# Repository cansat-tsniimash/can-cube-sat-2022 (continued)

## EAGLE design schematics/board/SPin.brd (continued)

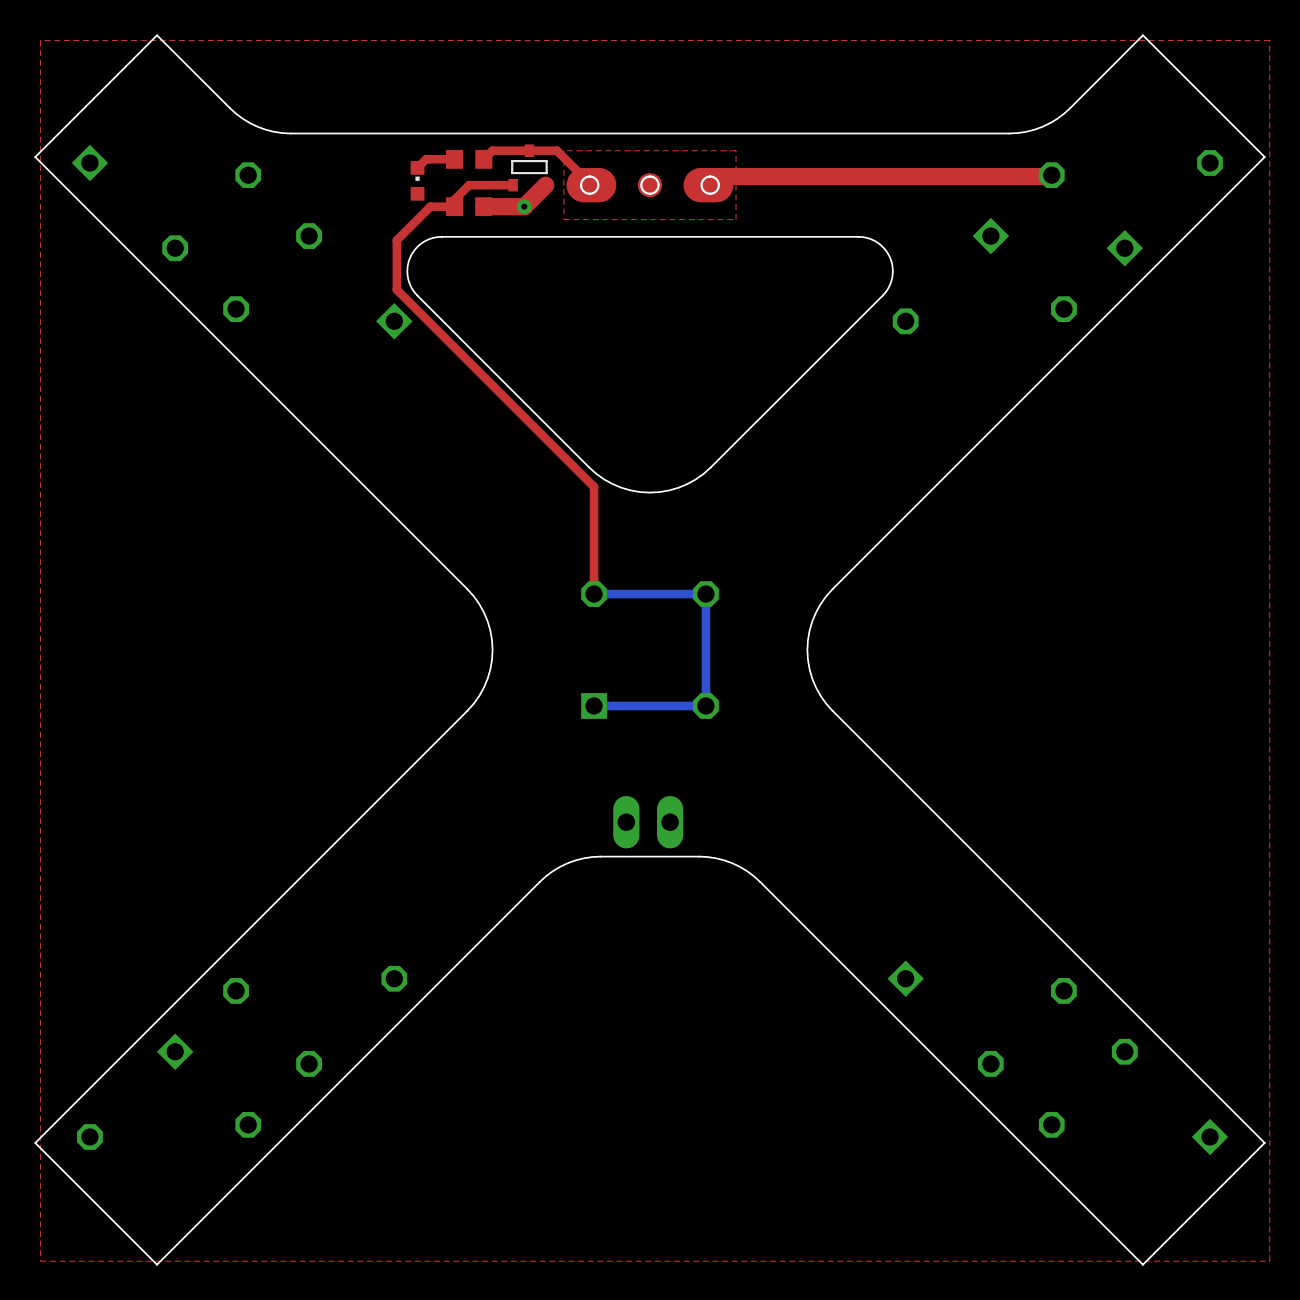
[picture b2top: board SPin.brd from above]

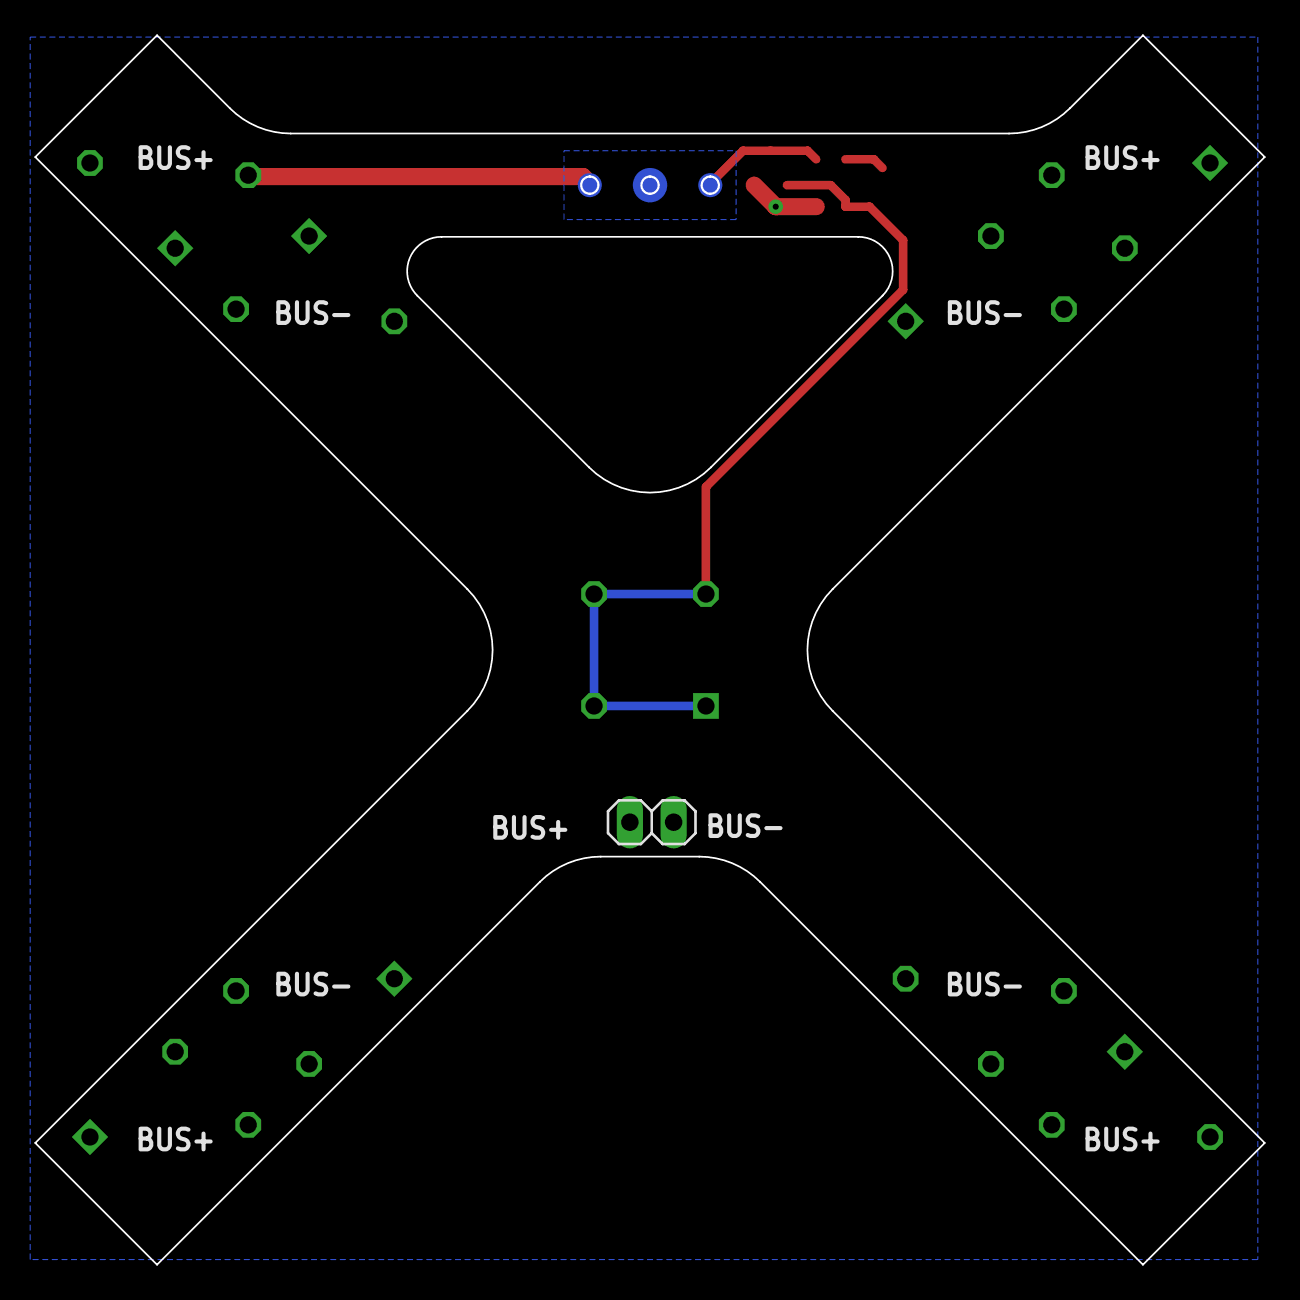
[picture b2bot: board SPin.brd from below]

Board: 2 copper layers, 71.4 x 71.4 mm, 15 parts (9 on the bottom side), 5 nets.

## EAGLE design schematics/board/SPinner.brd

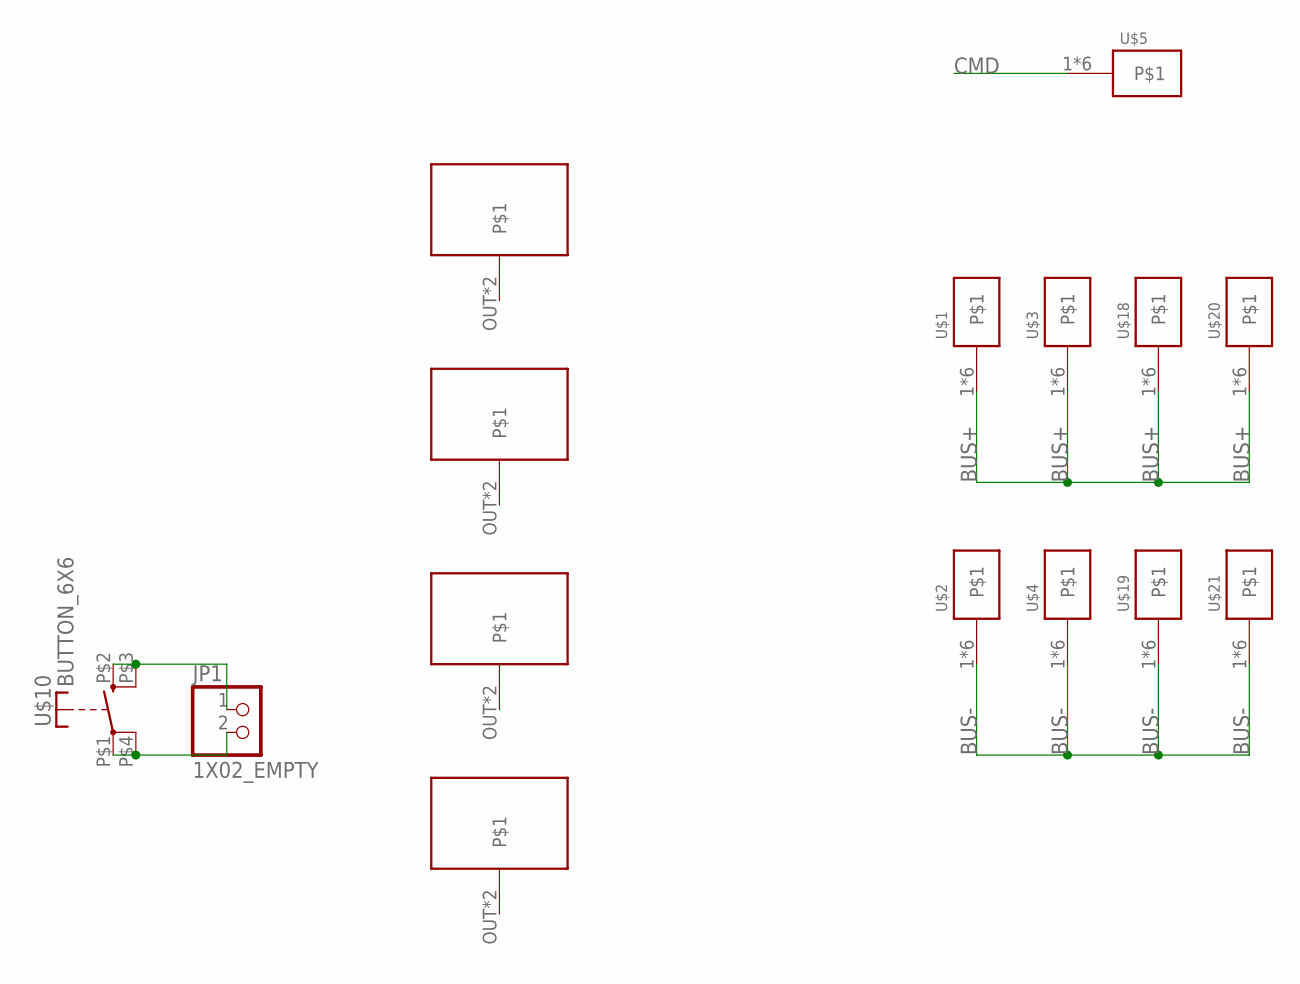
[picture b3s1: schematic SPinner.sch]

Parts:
JP1: 1X02_EMPTY
U$1, U$2, U$3, U$4, U$18, U$19, U$20, U$21: KCONNECT
U$5: KCONNECTQUAD; KCONNECT_QUAD
U$6, U$7, U$8, U$9: GRAFIT-PASSIVE
U$10: BUTTON_6X6

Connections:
BUS+: U$1.1, U$1.2, U$1.3, U$1.4, U$1.P$1, U$1.P$2, U$3.1, U$3.2, U$3.3, U$3.4, U$3.P$1, U$3.P$2, U$18.1, U$18.2, U$18.3, U$18.4, U$18.P$1, U$18.P$2, U$20.1, U$20.2, U$20.3, U$20.4, U$20.P$1, U$20.P$2
BUS-: U$2.1, U$2.2, U$2.3, U$2.4, U$2.P$1, U$2.P$2, U$4.1, U$4.2, U$4.3, U$4.4, U$4.P$1, U$4.P$2, U$19.1, U$19.2, U$19.3, U$19.4, U$19.P$1, U$19.P$2, U$21.1, U$21.2, U$21.3, U$21.4, U$21.P$1, U$21.P$2
CMD: U$5.1, U$5.2, U$5.3, U$5.4, U$5.P$1, U$5.P$2
unnamed: JP1.1, U$10.P$2 (S), U$10.P$3 (S)
unnamed: JP1.2, U$10.P$1, U$10.P$4

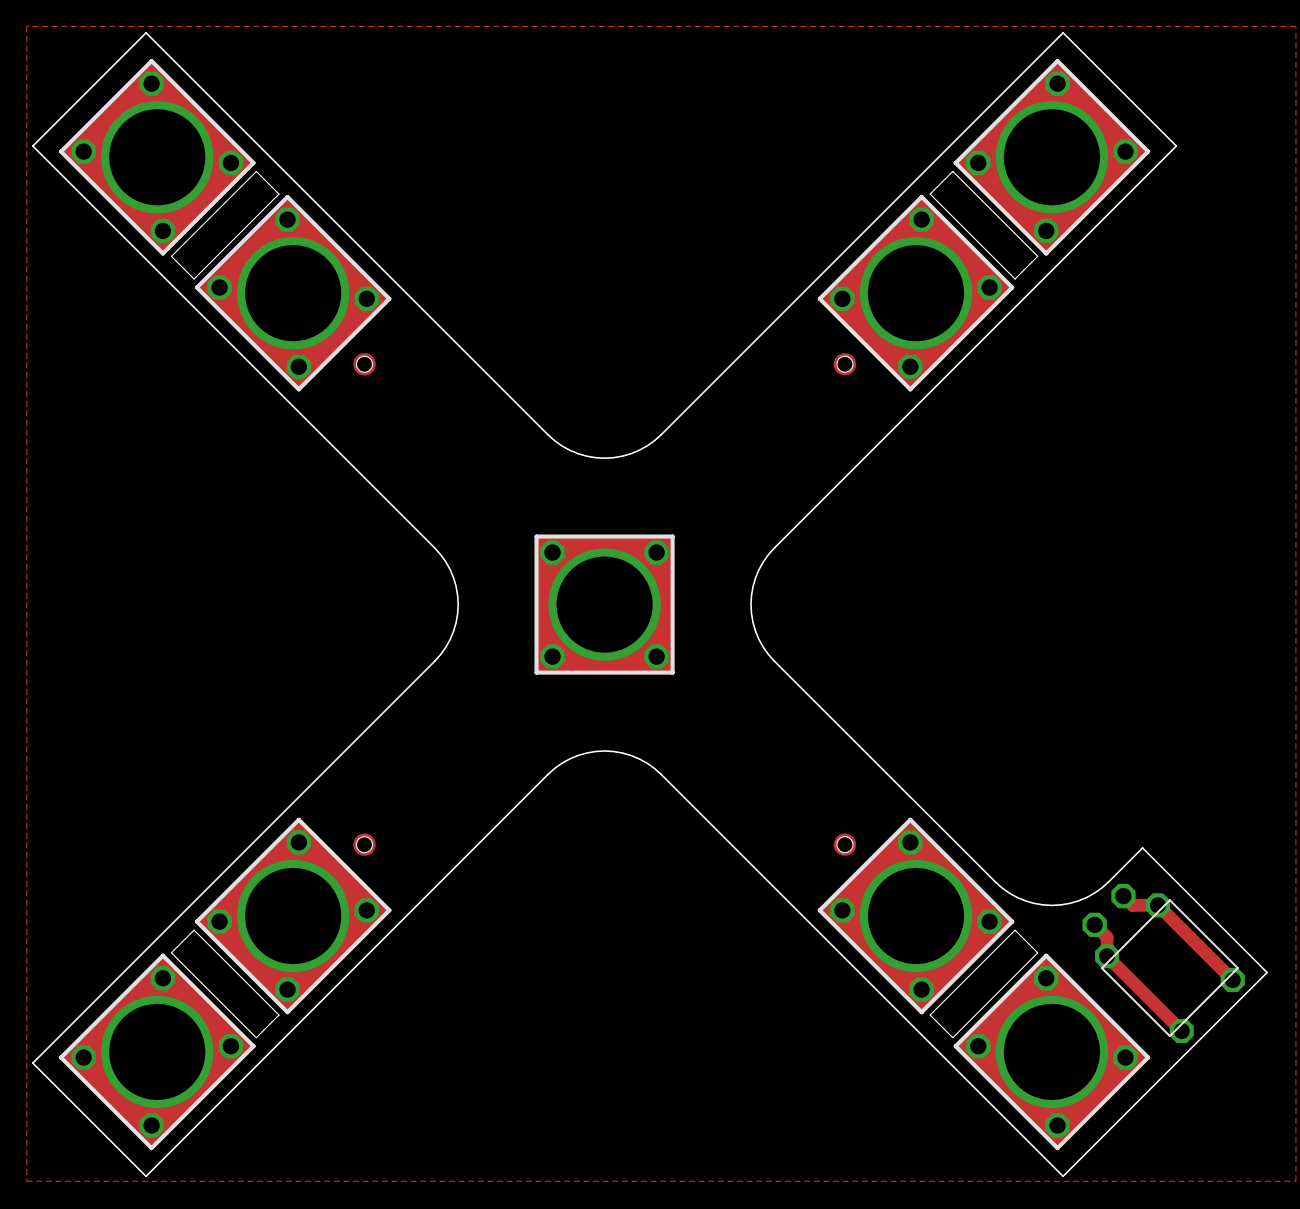
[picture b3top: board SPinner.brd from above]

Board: 2 copper layers, 77.1 x 71.4 mm, 15 parts (0 on the bottom side), 5 nets.

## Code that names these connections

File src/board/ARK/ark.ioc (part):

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Mcu.Name=STM32F103C(8-B)Tx
Mcu.Package=LQFP48
Mcu.UserName=STM32F103C8Tx
PA0-WKUP.GPIOParameters=GPIO_Speed,PinState,GPIO_PuPd,GPIO_Label,GPIO_ModeDefaultOutputPP
PA0-WKUP.GPIO_Label=BMS4
PA0-WKUP.GPIO_ModeDefaultOutputPP=GPIO_MODE_OUTPUT_OD
PA0-WKUP.GPIO_PuPd=GPIO_NOPULL
PA0-WKUP.GPIO_Speed=GPIO_SPEED_FREQ_LOW
PA0-WKUP.PinState=GPIO_PIN_SET
PA0-WKUP.Signal=GPIO_Output
PA1.GPIOParameters=GPIO_Speed,PinState,GPIO_PuPd,GPIO_Label,GPIO_ModeDefaultOutputPP
PA1.GPIO_Label=BMS1
PA1.GPIO_ModeDefaultOutputPP=GPIO_MODE_OUTPUT_OD
PA1.GPIO_PuPd=GPIO_NOPULL
PA1.GPIO_Speed=GPIO_SPEED_FREQ_LOW
PA1.PinState=GPIO_PIN_SET
PA1.Signal=GPIO_Output
PA10.Mode=Asynchronous
PA10.Signal=USART1_RX
PA13.Mode=Serial_Wire
PA13.Signal=SYS_JTMS-SWDIO
PA14.Mode=Serial_Wire
PA14.Signal=SYS_JTCK-SWCLK
PA15.GPIOParameters=GPIO_Label
PA15.GPIO_Label=DC_DC
PA15.Signal=GPIO_Output
PA2.GPIOParameters=GPIO_Speed,PinState,GPIO_PuPd,GPIO_Label,GPIO_ModeDefaultOutputPP
PA2.GPIO_Label=BMS2
PA2.GPIO_ModeDefaultOutputPP=GPIO_MODE_OUTPUT_OD
PA2.GPIO_PuPd=GPIO_NOPULL
PA2.GPIO_Speed=GPIO_SPEED_FREQ_LOW
PA2.PinState=GPIO_PIN_SET
PA2.Signal=GPIO_Output
PA3.GPIOParameters=GPIO_Label
PA3.GPIO_Label=TIME
PA3.Signal=GPXTI3
PA4.GPIOParameters=GPIO_Label,GPIO_Speed,GPIO_ModeDefaultOutputPP,PinState,GPIO_PuPd
PA4.GPIO_Label=OW
PA4.GPIO_ModeDefaultOutputPP=GPIO_MODE_OUTPUT_OD
PA4.GPIO_PuPd=GPIO_NOPULL
PA4.GPIO_Speed=GPIO_SPEED_FREQ_HIGH
PA4.PinState=GPIO_PIN_SET
PA4.Signal=GPIO_Output
PA5.GPIOParameters=GPIO_Label
PA5.GPIO_Label=ROZE1
PA5.Signal=GPIO_Input
PA6.GPIOParameters=GPIO_Label
PA6.GPIO_Label=ROZE2
PA6.Signal=GPIO_Input
PA7.GPIOParameters=GPIO_Label
PA7.GPIO_Label=ROZE3
PA7.Signal=GPIO_Input
PA8.GPIOParameters=GPIO_Label
PA8.GPIO_Label=PFI_C
PA8.Signal=GPXTI8
PA9.Mode=Asynchronous
PA9.Signal=USART1_TX
PB0.GPIOParameters=GPIO_Label
PB0.GPIO_Label=ROZE4
PB0.Signal=GPIO_Input
PB10.GPIOParameters=GPIO_Label,GPIO_Pu
PB10.GPIO_Label=SCL
PB10.GPIO_Pu=GPIO_PULLUP
PB10.Mode=I2C
PB10.Signal=I2C2_SCL
PB11.GPIOParameters=GPIO_Label,GPIO_Pu
PB11.GPIO_Label=SDA
PB11.GPIO_Pu=GPIO_PULLUP
PB11.Mode=I2C
PB11.Signal=I2C2_SDA
PB12.GPIOParameters=GPIO_Label,GPIO_Speed,GPIO_ModeDefaultOutputPP,PinState,GPIO_PuPd
PB12.GPIO_Label=LED
PB12.GPIO_ModeDefaultOutputPP=GPIO_MODE_OUTPUT_OD
PB12.GPIO_PuPd=GPIO_NOPULL
PB12.GPIO_Speed=GPIO_SPEED_FREQ_LOW
PB12.PinState=GPIO_PIN_SET
PB12.Signal=GPIO_Output
PB13.GPIOParameters=GPIO_Label
PB13.GPIO_Label=INT_C
PB13.Signal=GPXTI13
PB14.GPIOParameters=GPIO_Label
PB14.GPIO_Label=PGB_C
PB14.Signal=GPXTI14
PB15.GPIOParameters=GPIO_Label
PB15.GPIO_Label=PGS_C
PB15.Signal=GPXTI15
PB4.GPIOParameters=GPIO_Label
PB4.GPIO_Label=PFI_D
PB4.Signal=GPXTI4
PB5.GPIOParameters=GPIO_Label
PB5.GPIO_Label=INT_D
PB5.Signal=GPXTI5
PB6.GPIOParameters=GPIO_Label
PB6.GPIO_Label=PGB_D
PB6.Signal=GPXTI6
PB7.GPIOParameters=GPIO_Label
PB7.GPIO_Label=PGS_D
PB7.Signal=GPXTI7
PB8.GPIOParameters=GPIO_Label,GPIO_Pu
PB8.GPIO_Label=SCLTM
PB8.GPIO_Pu=GPIO_PULLUP
PB8.Mode=I2C
PB8.Signal=I2C1_SCL
PB9.GPIOParameters=GPIO_Label,GPIO_Pu
PB9.GPIO_Label=SDATM
PB9.GPIO_Pu=GPIO_PULLUP
PB9.Mode=I2C
PB9.Signal=I2C1_SDA
PC13-TAMPER-RTC.GPIOParameters=GPIO_Speed,PinState,GPIO_PuPd,GPIO_Label,GPIO_ModeDefaultOutputPP
PC13-TAMPER-RTC.GPIO_Label=BMS5
PC13-TAMPER-RTC.GPIO_ModeDefaultOutputPP=GPIO_MODE_OUTPUT_OD
PC13-TAMPER-RTC.GPIO_PuPd=GPIO_NOPULL
PC13-TAMPER-RTC.GPIO_Speed=GPIO_SPEED_FREQ_LOW
PC13-TAMPER-RTC.PinState=GPIO_PIN_SET
PC13-TAMPER-RTC.Signal=GPIO_Output
PC14-OSC32_IN.GPIOParameters=GPIO_Speed,PinState,GPIO_PuPd,GPIO_Label,GPIO_ModeDefaultOutputPP
PC14-OSC32_IN.GPIO_Label=BMS6
PC14-OSC32_IN.GPIO_ModeDefaultOutputPP=GPIO_MODE_OUTPUT_OD
PC14-OSC32_IN.GPIO_PuPd=GPIO_NOPULL
PC14-OSC32_IN.GPIO_Speed=GPIO_SPEED_FREQ_LOW
PC14-OSC32_IN.PinState=GPIO_PIN_SET
PC14-OSC32_IN.Signal=GPIO_Output
PC15-OSC32_OUT.GPIOParameters=GPIO_Speed,PinState,GPIO_PuPd,GPIO_Label,GPIO_ModeDefaultOutputPP
PC15-OSC32_OUT.GPIO_Label=BMS3
PC15-OSC32_OUT.GPIO_ModeDefaultOutputPP=GPIO_MODE_OUTPUT_OD
PC15-OSC32_OUT.GPIO_PuPd=GPIO_NOPULL
PC15-OSC32_OUT.GPIO_Speed=GPIO_SPEED_FREQ_LOW
PC15-OSC32_OUT.PinState=GPIO_PIN_SET
PC15-OSC32_OUT.Signal=GPIO_Output
RCC.SYSCLKFreq_VALUE=64000000
RCC.SYSCLKSource=RCC_SYSCLKSOURCE_PLLCLK
board=custom

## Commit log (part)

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2021-05-09 Замдляем I2C
2021-05-09 Тонкие настройки
2021-05-11 Зачатки проекта для имитатора барометров и прочего
2021-05-12 Добавлена шелкографика на плате БКУ
2021-05-12 Симуляция для алгоритма управления компрессором
2021-05-13 Исправлены тайминги отправки пакетов
2021-05-13 Добавлены герберы плат BKU и Debug
2021-05-14 Выставляется правильное время в сообщениях о диодах в синсе
2021-05-14 исправил какой-то косяк с тулчейном для синса
2021-05-15 Коррекция времени работет
2021-05-15 Причесывание GPS в синсе, Работа еще не окончена
2021-05-15 Исправлено напряжение TCXO для радио, согласно мануалу (не очень понятно откуда он взялся...)
2021-05-16 ПН работа
2021-05-16 Очень неприятный баг, который опять пропустили из-за обилия варнингов
2021-05-16 Настройки тулчейна пейлоада опять сползли
2021-05-16 Убрал подозрительные места с работой по невыровненным членам структур. сырое значение MICS6814 теперь сырое значение АЦП, а измеренного сопротивления TODO: перебить поле на инт
2021-05-16 Чуточку причесаны ДНК и дозиметр
2021-05-16 Попытка сделать i2c линк правильно и подключить его к комиссару
2021-05-19 Подтяжка на UART4 RX (отладочный) для пейлоада
2021-05-19 Исправлены баги на пл
2021-05-19 Исправлены ошибки подсчета RSSI в радио-сервере
2021-05-22 Убрал подтяжку
2021-05-22 Отовсюду убраны подтяжки, в пейлоаде выловлено несколько багов и починнен (вроде как) файл проекта
2021-05-22 Вернул таск управления батарейками. Он был отключен здесь 438129f4b1aff372015f85f637c77f4349155d02
2021-05-22 Вернул 2 ины. Были убраны здесь b21d58dcb7bf618727028e3295f56fd343d0ac48
2021-05-22 Баг с дискретной темературой
2021-05-24 Исправлено UB в драйвере радио. Добавлены RSSI в сервер-радио
2021-05-25 Причесал и чуток запараноил драйвер радио
2021-05-26 Убрал варнинги из драйвера радио
2021-05-26 Дополнительный пин для синхронизации времени
2021-05-28 Нехороший косяк в пейлоаде с i2c-линком и мелкая правка утилиты для разбора метаданных ZMQ
2021-05-28 Второе рождение проекта для отладки i2c-link-а на f4
2021-05-29 Добавлены адреса 1w датчиков для арка на стенде
2021-05-29 Да здраствет передача земля - борт
2021-05-29 Исправлена очень страшная бага с одновремененым доступом к шине
2021-05-29 I2C линк доведен до уровня на котором он может быть внедрен в проекты бортового ПО
2021-05-29 Миграция пейлоада на новый i2c-link
2021-05-29 Миграция БКУ новый i2c-link протокол
2021-05-30 Актуализация для отладки its-i2c линка на stm32f1
2021-05-30 Обновление i2c-link драйвера в проектах ПО бортовых компов с поддержкой f1 и f4
2021-05-30 Ошибка в расчете собственной температуры пейлоада
2021-05-31 Переезд наземных утилиток в отдельную папочку
2021-06-03 Дописал гитингор для тестовых проектов
2021-06-03 Готова плата RADIO и переделана плата AB
2021-06-03 Новый i2c линк отлажен на синсе
2021-06-03 Новый драйвер АЦП для полезной нагрузки с компенсацией по напряжению на VDDA
2021-06-03 Отчёты комиссара в полезной нагрузке
2021-06-04 Новый алгоритм управления компрессором
2021-06-04 Добавление стабильного времени во все сообщения полезной нагрузки
2021-06-05 Обновлен счетчик резетов, добавлена причина резета. Перетянуты функции чтения и записи в бэкап регистр RTC из LL драйвера
2021-06-05 Мелкие баги в комиссаре
2021-06-05 БКУ в реалиях стабильного времени в каждом сообщении
2021-06-05 Время теперь синхронизиурется
2021-06-05 Новая политика службы времени на полезной нагрузке и расширение её статуса
2021-06-05 Попытка добавить ины
2021-06-05 Улучшения политики работы со службой времени на полезной нагрузке
2021-06-08 MICS6814 меряет на всех доступных плечах
2021-06-09 Не то, чтобы это было страшные баги с радио, но мелочи, которые требовали правки
2021-06-10 Очень нехорошие баги в brd части радио на бку
2021-06-10 Попытка избежать гонки с завершением rx режима с радио на борту
2021-06-10 Истеричные попытки наладить радиоканал
2021-06-10 Грядет большая революция в драйвере радио
2021-06-11 Добавлен вочдог на sins. Необходимо проверить его работу
2021-06-11 Изменены настройки частот для работы с платой
2021-06-11 ARK переехал на плату. Настроен HSE
2021-06-11 обновлены LL драйверы для rtc-fromgps
2021-06-12 Кажется, лучше не становится
2021-06-12 Все еще бьет данные
2021-06-12 Доведено до сборки везде. Кажется, все проблемы устранены
2021-06-12 Разные улучшайзеры
2021-06-12 Ины работают (только макс значение тока надо редактировать)
2021-06-12 Рабочее радио
2021-06-12 Еще попытки работать
2021-06-12 Обновлен комиссар
2021-06-12 Управление питанием теперь значительно проще
2021-06-15 Очередная переделка сервера-радио
2021-06-16 Теперь дравер ины не противный
2021-06-16 Проект для отработки CSS на f4 (и оно даже более менее работает, осталось оформить)
2021-06-17 Размер коррекции в телеметрии полезной нагрузки
2021-06-17 Правильный подсчет размера коррекции времени
2021-06-17 Рабочие ины
2021-06-17 gettimeofday нельзя вызывать из прервания
2021-06-17 Логи теперь еще более безопасные
2021-06-19 Больше дсок!
2021-06-19 Нагреватеели теперь работают
2021-06-19 Оказывается, порядок сдивговых регистров другой :(
2021-06-20 Проекты для ОЧЕРЕДНОЙ отработки лоры
2021-06-20 Правки мелких и не сильно существенных багов в драйвере радио
2021-06-23 Больше дсок
2021-06-23 Больше логов
2021-06-23 ОБНОВЛЕНИЕ МАВЛИНКА. Ремонт службы времени на пейлоаде и расширенная диагностика в телеметрии.
2021-06-24 Ины работают только на высоких частотах
2021-06-24 Пофискил время
2021-06-24 Новый timebase для синса и выдача сообщения со временем не у границы секунды
2021-06-25 Запуск с RTC. Работает
2021-06-25 Обработка новых команд
2021-06-25 Записываю номер последней команды
2021-06-25 Добавлено монотонное время в пакеты ark
2021-06-25 Заготовки для безопасного радио
2021-06-26 исправлена лампочка для платы ark
2021-06-26 Клок пейлоада для боевой платы
2021-06-26 Реализована поддержка CSS на SINS
2021-06-26 Реализована поддержка CSS на PAYLOAD
2021-06-26 Чистим
2021-06-29 Адреса на пейлоаде исправлены
2021-06-29 Попытка уменьшить лаг отправки времени с синса
2021-06-29 Забытая диагностика
2021-06-29 Таакая частота вроде тоже работает
2021-06-29 Комментарии к службе времени на синсе
2021-07-02 Больше дебаа богу дебага
2021-07-02 Заготовка для модуля, управляющего питанием
2021-07-02 Частота синса исправлена
2021-07-02 Исправлены баги радио
2021-07-03 Комиссар теперь отправляет сообщения
2021-07-03 Исправлен пакет с ошибками
2021-07-03 Убраны варнинги в ARK
2021-07-03 Вбил параметры резисторов mics6814
2021-07-03 Добавлено ограничение по чатоте отправки сообщения
2021-07-03 Коррекция температур для ДНК
2021-07-03 Еще одна очень нехорошая ошибка в коде дозиметра
2021-07-03 Мелкие изменения
2021-07-03 Починил MSP
2021-07-03 Наконец-то дал этому модулю нормальное имя
2021-07-06 ой! Это должно было быть в прошлом коммите
2021-07-07 Разделение кода на функции для улчшения читаемости
2021-07-07 Забытое время пакета
2021-07-07 Фиксим статистику времени
2021-07-07 Кажется теперь все параметры mics6814 вбиты правильно
2021-07-07 Подправлена частота и оффсеты выдачи сообщений пейлоада
2021-07-07 Созданы гербер файлы AB и RADIO
2021-07-07 Починен сброс для sx126x на БКУ
2021-07-12 Исправлена сборка синса в релизе (толком не проверено, но хотябы собирается)
2021-07-12 Добавки к AHRS
2021-07-12 Закончен солнечный датчик
2021-09-01 Исправления драйвера ины и использование правильных сопротивлений
2021-09-03 Чаще замеряем ины
2021-09-08 Починили термодатчики
2021-09-08 Попытки с АЦП
2021-09-11 Реворк I2C таска на арке
2021-09-11 !MAVLINK! Новое сообщение для солнечного датчика
2021-09-11 напряжения с арка в вольтах а не в милливольтах
2021-09-11 Ины теперь должны перезагружаться при получении от них плохих данных
2021-09-11 Правильная обработка флагов GPS
2021-09-15 OW теперь на другом пине, так как старый поломался
2021-09-15 Обидные баги синса
2021-09-15 СД карта теперь быстрее восстанавливается
2021-09-15 Убрана подтяжка на OW
2021-09-15 Этот дефайн больше не используется
2021-09-16 Добавлен вспомогательный кодик для тестов компрессора
2021-09-18 ОМЕРЗИТЕЛЬНЫЙ БАГ В ДРАЙВЕРЕ РАДИО
2021-09-18 Posix структура tm просто отвратительна
2021-09-24 Исправляем баги со временем на АРКе
2021-09-24 Подправленные данные фотодиодов
2021-09-25 Реворк рекавера i2c шины с инами на арке
2021-10-01 Исправленный солнечный датчик
2021-10-01 Калибровка магнитометра
2021-10-01 ОБНОВЛЕН МАВЛИНК Увеличена частота сбороса состояния компрессора на пейлоаде Добавлены подробные параметры включения выключения компрессора на пейлоаде Увелчен размер очереди i2c сообщений в пейлоаде
2021-10-01 Добавлена отсечка показаний bme280 от алгоритмов управления, в случае, если его показания уходят за пределы допустимых по даташиту
2021-10-02 Обновлен Мавлинк, добавлен недобавленный файл, улучшен ИНС
2021-10-02 Тише!
2021-10-03 Работаем над управлением компрессора в условиях хорошей утечки из гермообъема
2021-10-03 Моделирование минимальной модификации
2021-10-04 Апгрейд алгоритма управления компрессором на пейлоаде
2021-10-05 Палетная телеметрия SD
2021-10-05 Перемещение старой телеметрии
2022-02-17 команды для создания репозитория
2022-03-17 Добавлены платы SP
2022-03-19 Добавил наработки по ccsds
2022-03-19 Наработки по map
2022-03-20 Проверил платы SPinner и SPin,внес декоративные правки
2022-03-20 Залил новую документацию на зимнюю сессию. Убрал устаревшую
2022-03-30 Пакет теперь целиком передается на землю
2022-03-30 Обрабатываем отдельно случай пустого tfdf в map
2022-03-30 Стырил файлы из старого проекта
2022-03-30 Подготовил все для сериалайзинга фрейма
2022-04-05 Попытки доделать распаковку фреймов
2022-04-12 Пытаюсь добавить сообщения ГПС
2022-04-14 Добавила таки сообщение переменной длинны
2022-04-21 MAPA работает в обе стороны!
2022-04-23 Интеграция мавлинка в новом стиле
2022-04-23 Миграция на новую CubeIDE
2022-04-25 Правки в преобразовании типов. битовый вариант маски заменила на хексовый
2022-04-25 Тестики
2022-04-26 Модель компрессора чуточку подогнана под настоящее положение вещей
2022-04-27 Наколдовала отправку новых сообщений. Надеюсь это сработает
2022-04-30 Проект БКУ доведен до компиляции
2022-05-02 Готова схема платы АРК
2022-05-05 Новенький парсер
2022-05-05 Добавили новое сообщени в синсы (вроде)
2022-05-05 Пейлоад качает компесссором в покое для отладки (с другими цифрами)
2022-05-07 Циклобуфер работает!
2022-05-11 Работа Сергея
2022-05-12 Улучшение таймингов радио
2022-05-16 Разведена плата АРК
2022-05-19 Дописала сообщения в костыль + исправление бага
2022-05-21 Добавлены компоненты в библиотеку CanCubeSat
2022-05-21 Откомпилировала и исправила баги
2022-05-21 Обновил мавлинк, починил калибровку
2022-05-22 Переделал крепление солнечной панели под кнопку и новую пружину
2022-05-25 Обмазался симейками
2022-05-25 MAPP работает в обе стороны!
2022-06-15 Боевые режимы радио на БКУ (ничего не работает)
2022-06-15 Обновление мавлинка и фикс багов тайминга радио
2022-06-15 Поймано пропавшее сообщение NAV-SVSI. Правда пока не на борту. И вообще UBX парсеры несколько переосмыслены
2022-06-16 Красота для отладки GPS
2022-06-16 Увеличено время вотчдога для пейлоада
2022-06-18 SINS больше не заваливает шину сообщениями комиссара
2022-06-24 Обновила сообщение SINS_RXMSVSI. Оно собирается. В бою не проверялось
2022-06-28 Прием работает
2022-07-01 Эксперименты с таймнгами радио
2022-07-03 Тестим радио
2022-07-03 Пофиксил радио
2022-07-05 Электрические параметры в телеметрии БКУ больше не путешествуют назад во времени по шкале time_steady. Жаль, что это были воображаемые путешествия :c
2022-07-06 Актуализация скриптов и графопостроители
2022-07-06 Лучший набор телеметрии на ЗЕМЛЕ
2022-07-06 требуемое для разбора
2022-07-06 Новые графики
2022-07-06 Добавил секунды туда сюда
2022-07-06 Анализ радио канала по дистанции от аппарата
2022-07-06 Анализ потерь пакетов
2022-07-06 Анализ RSSI и SNR на одном графике
2022-07-07 Разные правки и графики температуры
2022-12-23 Добавил графики
2023-04-18 Добавлен скрипт для графиков солнечного датчика
